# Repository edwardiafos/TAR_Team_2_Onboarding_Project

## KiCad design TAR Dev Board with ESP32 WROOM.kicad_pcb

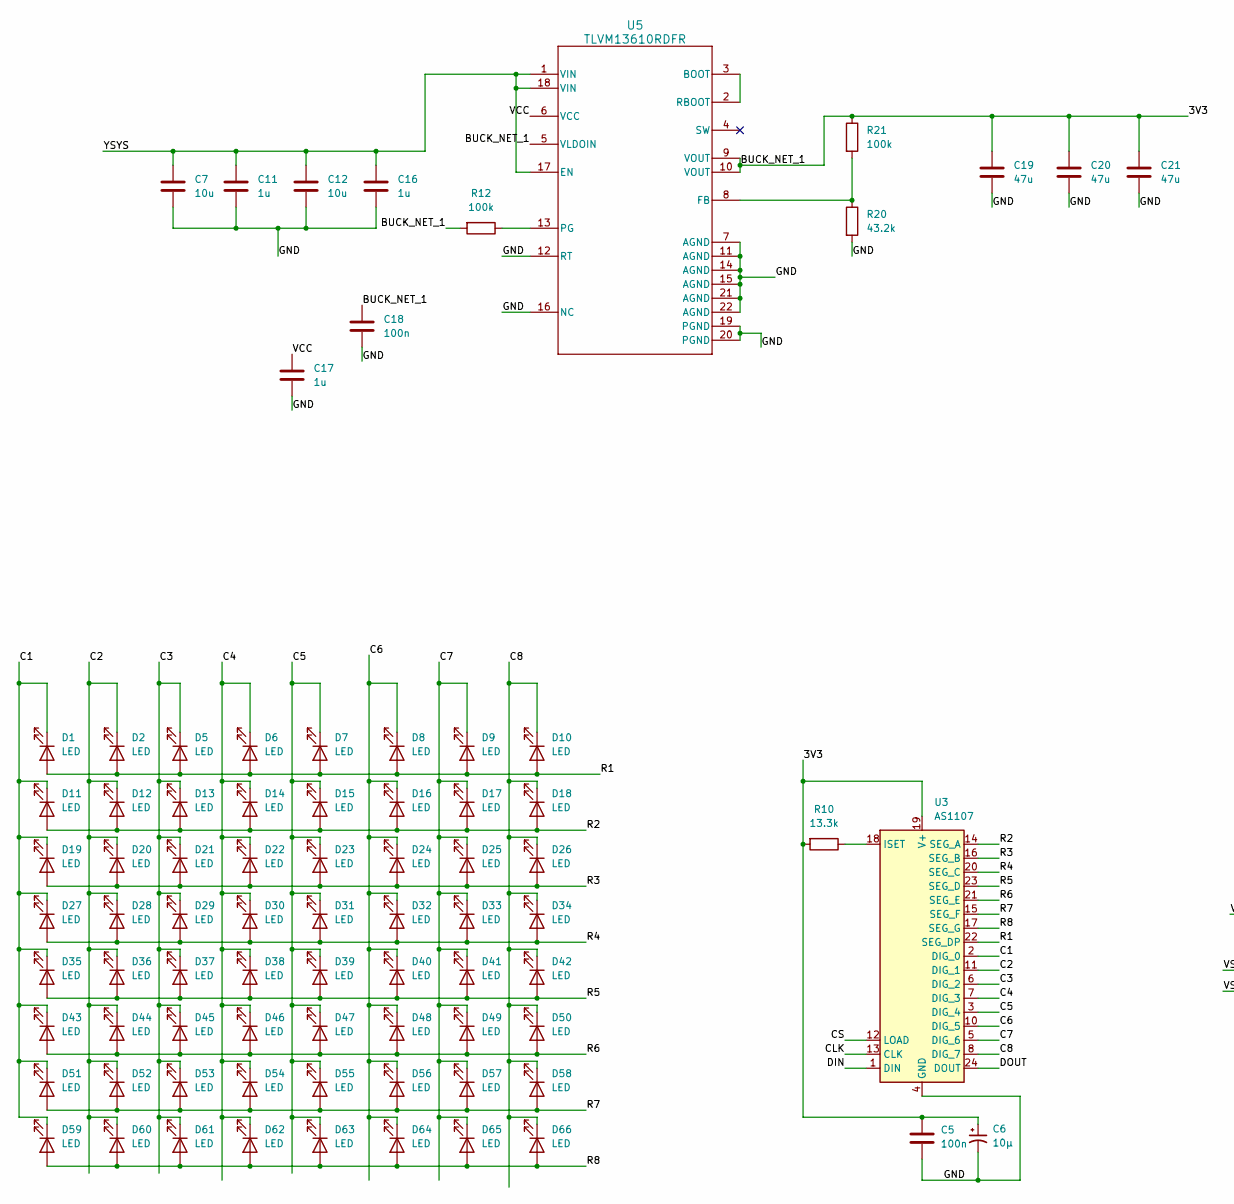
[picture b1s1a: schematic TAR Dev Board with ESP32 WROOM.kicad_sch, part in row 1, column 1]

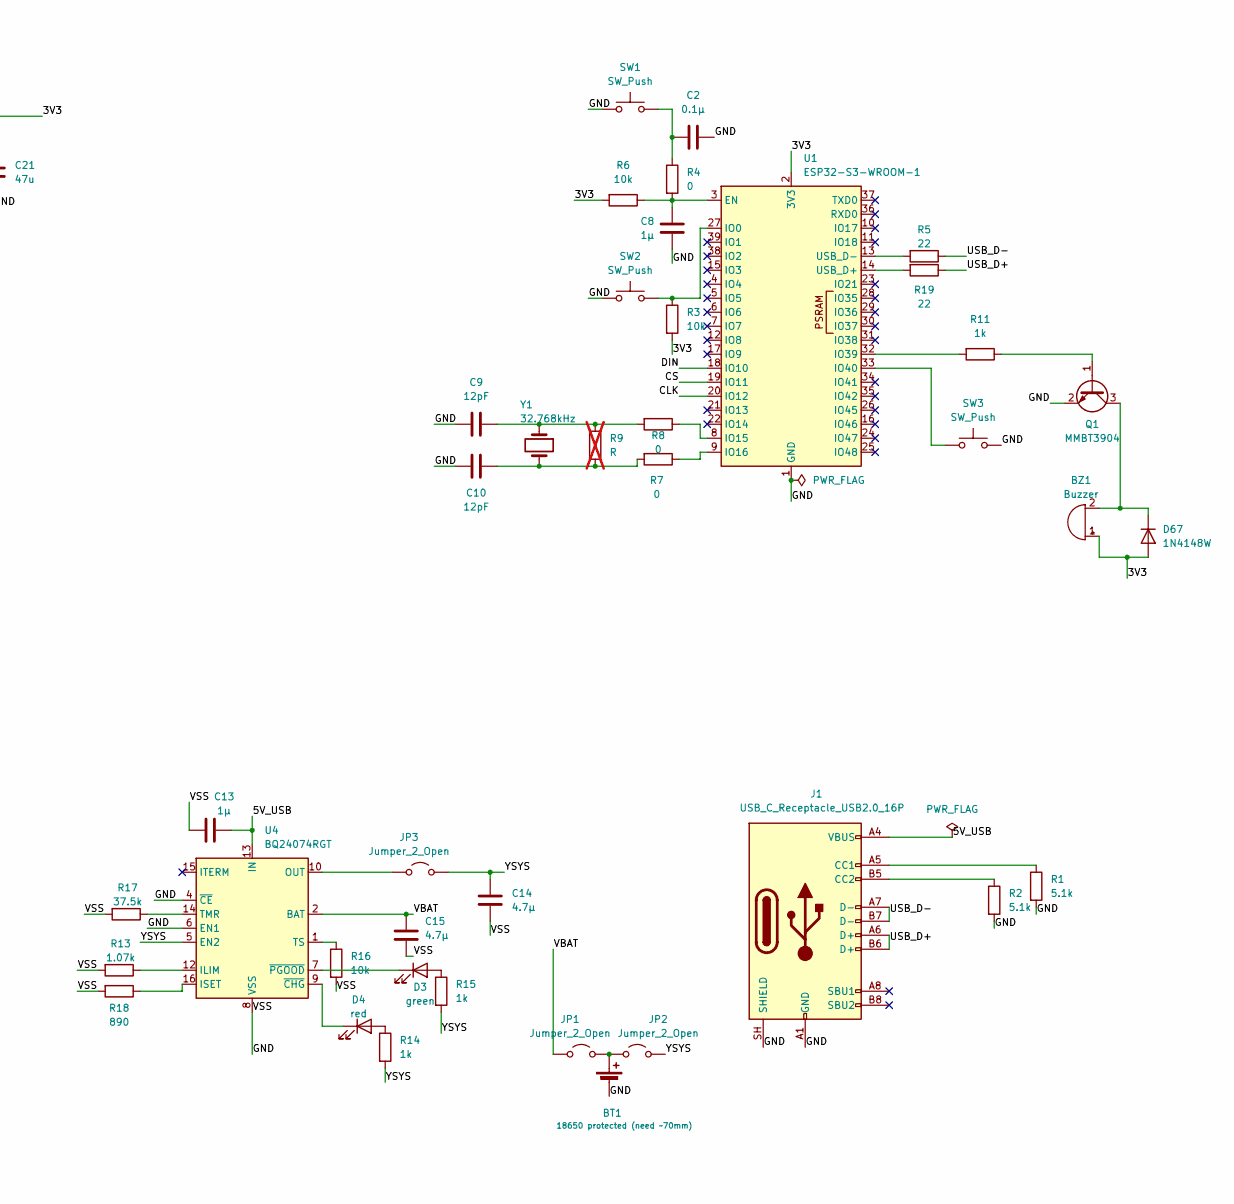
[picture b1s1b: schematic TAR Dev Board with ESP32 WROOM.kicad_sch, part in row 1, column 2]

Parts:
BT1: 18650 protected (need ~70mm); BatteryHolder_Keystone_1042_1x18650
BZ1: Buzzer; Buzzer_12x9.5RM7.6
C2: 0.1μ; C_0805_2012Metric
C5, C18: 100n; C_0805_2012Metric
C6: 10μ; CP_Elec_4x5.4
C7, C12: 10u; C_1206_3216Metric
C8: 1µ; C_0805_2012Metric
C9, C10: 12pF; C_0603_1608Metric
C11, C16, C17: 1u; C_0805_2012Metric
C13: 1μ; C_0805_2012Metric
C14, C15: 4.7μ; C_1206_3216Metric
C19, C20, C21: 47u; C_1206_3216Metric
D1, D2, D5, D6, D7, D8, D9, D10, D11, D12, D13, D14, D15, D16, D17, D18, D19, D20, D21, D22, D23, D24, D25, D26, D27, D28, D29, D30, D31, D32, D33, D34, D35, D36, D37, D38, D39, D40, D41, D42, D43, D44, D45, D46, D47, D48, D49, D50, D51, D52, D53, D54, D55, D56, D57, D58, D59, D60, D61, D62, D63, D64, D65, D66: LED; LED_0805_2012Metric
D3: green; LED_0805_2012Metric
D4: red; LED_0805_2012Metric
D67: 1N4148W; D_SOD-123
J1: USB_C_Receptacle_USB2.0_16P; USB_C_Receptacle_HRO_TYPE-C-31-M-12
JP1, JP2, JP3: Jumper_2_Open; PinHeader_1x02_P2.54mm_Vertical
Q1: MMBT3904; SOT-23
R1, R2: 5.1k; R_0805_2012Metric
R3, R6, R16: 10k; R_0805_2012Metric
R4, R7, R8: 0; R_0805_2012Metric
R5, R19: 22; R_0805_2012Metric
R9: R; R_0805_2012Metric; not fitted
R10: 13.3k; R_0805_2012Metric
R11, R14, R15: 1k; R_0805_2012Metric
R12, R21: 100k; R_0805_2012Metric
R13: 1.07k; R_0805_2012Metric
R17: 37.5k; R_0805_2012Metric
R18: 890; R_0805_2012Metric
R20: 43.2k; R_0805_2012Metric
SW1, SW2, SW3: SW_Push; SW_PUSH_6mm
U1: ESP32-S3-WROOM-1
U3: AS1107; SOIC-24W_7.5x15.4mm_P1.27mm
U4: BQ24074RGT; VQFN-16-1EP_3x3mm_P0.5mm_EP1.8x1.8mm_ThermalVias
U5: TLVM13610RDFR; TLVM13610
Y1: 32.768kHz; Crystal_SMD_3215-2Pin_3.2x1.5mm

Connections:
/5V_USB: C13.1, J1.A4 (VBUS), J1.A9 (VBUS), J1.B4 (VBUS), J1.B9 (VBUS), U4.13 (IN)
/<NO NET>: BZ1.1 (+), C5.1, C6.1, C18.1, C19.1, C20.1, C21.1, D67.2 (A), R3.2, R6.2, R10.2, R12.2, R21.1, U1.2 (3V3), U3.19 (V+), U5.5 (VLDOIN), U5.9 (VOUT), U5.10 (VOUT)
/C1: D1.1 (K), D11.1 (K), D19.1 (K), D27.1 (K), D35.1 (K), D43.1 (K), D51.1 (K), D59.1 (K), U3.2 (DIG_0)
/C2: D2.1 (K), D12.1 (K), D20.1 (K), D28.1 (K), D36.1 (K), D44.1 (K), D52.1 (K), D60.1 (K), U3.11 (DIG_1)
/C3: D5.1 (K), D13.1 (K), D21.1 (K), D29.1 (K), D37.1 (K), D45.1 (K), D53.1 (K), D61.1 (K), U3.6 (DIG_2)
/C4: D6.1 (K), D14.1 (K), D22.1 (K), D30.1 (K), D38.1 (K), D46.1 (K), D54.1 (K), D62.1 (K), U3.7 (DIG_3)
/C5: D7.1 (K), D15.1 (K), D23.1 (K), D31.1 (K), D39.1 (K), D47.1 (K), D55.1 (K), D63.1 (K), U3.3 (DIG_4)
/C6: D8.1 (K), D16.1 (K), D24.1 (K), D32.1 (K), D40.1 (K), D48.1 (K), D56.1 (K), D64.1 (K), U3.10 (DIG_5)
/C7: D9.1 (K), D17.1 (K), D25.1 (K), D33.1 (K), D41.1 (K), D49.1 (K), D57.1 (K), D65.1 (K), U3.5 (DIG_6)
/C8: D10.1 (K), D18.1 (K), D26.1 (K), D34.1 (K), D42.1 (K), D50.1 (K), D58.1 (K), D66.1 (K), U3.8 (DIG_7)
/CLK: U1.20 (IO12), U3.13 (CLK)
/CS: U1.19 (IO11), U3.12 (LOAD)
/DIN: U1.18 (IO10), U3.1 (DIN)
/DOUT: U3.24 (DOUT)
/GND: BT1.2 (-), C2.1, C5.2, C6.2, C7.2, C8.2, C9.2, C10.2, C11.2, C12.2, C13.2, C14.2, C15.2, C16.2, C17.2, C18.2, C19.2, C20.2, C21.2, J1.A1 (GND), J1.A12 (GND), J1.B1 (GND), J1.B12 (GND), J1.SH (SHIELD), Q1.2 (E), R1.2, R2.2, R13.2, R16.2, R17.2, R18.2, R20.2, SW1.1, SW2.1, SW3.2, U1.1 (GND), U1.40 (GND), U1.41 (GND), U3.4 (GND), U3.9 (GND), U4.4 (~CE), U4.6 (EN1), U4.8 (VSS), U4.17 (VSS), U5.7 (AGND), U5.11 (AGND), U5.12 (RT), U5.14 (AGND), U5.15 (AGND), U5.16 (NC), U5.19 (PGND), U5.20 (PGND), U5.21 (AGND), U5.22 (AGND)
/R1: D1.2 (A), D2.2 (A), D5.2 (A), D6.2 (A), D7.2 (A), D8.2 (A), D9.2 (A), D10.2 (A), U3.22 (SEG_DP)
/R2: D11.2 (A), D12.2 (A), D13.2 (A), D14.2 (A), D15.2 (A), D16.2 (A), D17.2 (A), D18.2 (A), U3.14 (SEG_A)
/R3: D19.2 (A), D20.2 (A), D21.2 (A), D22.2 (A), D23.2 (A), D24.2 (A), D25.2 (A), D26.2 (A), U3.16 (SEG_B)
/R4: D27.2 (A), D28.2 (A), D29.2 (A), D30.2 (A), D31.2 (A), D32.2 (A), D33.2 (A), D34.2 (A), U3.20 (SEG_C)
/R5: D35.2 (A), D36.2 (A), D37.2 (A), D38.2 (A), D39.2 (A), D40.2 (A), D41.2 (A), D42.2 (A), U3.23 (SEG_D)
/R6: D43.2 (A), D44.2 (A), D45.2 (A), D46.2 (A), D47.2 (A), D48.2 (A), D49.2 (A), D50.2 (A), U3.21 (SEG_E)
/R7: D51.2 (A), D52.2 (A), D53.2 (A), D54.2 (A), D55.2 (A), D56.2 (A), D57.2 (A), D58.2 (A), U3.15 (SEG_F)
/R8: D59.2 (A), D60.2 (A), D61.2 (A), D62.2 (A), D63.2 (A), D64.2 (A), D65.2 (A), D66.2 (A), U3.17 (SEG_G)
/USB_D+: J1.A6 (D+), J1.B6 (D+), R19.1
/USB_D-: J1.A7 (D-), J1.B7 (D-), R5.1
/VBAT: C15.1, JP1.1 (A), U4.2 (BAT), U4.3 (BAT)
/VCC: C17.1, U5.6 (VCC)
/YSYS: C7.1, C11.1, C12.1, C14.1, C16.1, JP2.2 (B), JP3.2 (B), R14.2, R15.2, U4.5 (EN2), U5.1 (VIN), U5.17 (EN), U5.18 (VIN)
unnamed: BT1.1 (+), JP1.2 (B), JP2.1 (A)
unnamed: BZ1.2 (-), D67.1 (K), Q1.3 (C)
unnamed: C2.2, R4.1, SW1.2
unnamed: C9.1, R8.2, R9.1, Y1.1
unnamed: C10.1, R7.2, R9.2, Y1.2
unnamed: D3.2 (A), R15.1
unnamed: D3.1 (K), U4.7 (~PGOOD)
unnamed: D4.2 (A), R14.1
unnamed: D4.1 (K), U4.9 (~CHG)
unnamed: J1.A5 (CC1), R1.1
unnamed: J1.B5 (CC2), R2.1
unnamed: JP3.1 (A), U4.10 (OUT), U4.11 (OUT)
unnamed: Q1.1 (B), R11.1
unnamed: C8.1, R4.2, R6.1, U1.3 (EN)
unnamed: R3.1, SW2.2, U1.27 (IO0)
unnamed: R8.1, U1.8 (IO15)
unnamed: R7.1, U1.9 (IO16)
unnamed: R11.2, U1.32 (IO39)
unnamed: SW3.1, U1.33 (IO40)
unnamed: R19.2, U1.14 (USB_D+)
unnamed: R5.2, U1.13 (USB_D-)
unnamed: R10.1, U3.18 (ISET)
unnamed: R13.1, U4.12 (ILIM)
unnamed: R18.1, U4.16 (ISET)
unnamed: R17.1, U4.14 (TMR)
unnamed: R16.1, U4.1 (TS)
unnamed: U5.2 (RBOOT), U5.3 (BOOT)
unnamed: R20.1, R21.2, U5.8 (FB)
unnamed: R12.1, U5.13 (PG)

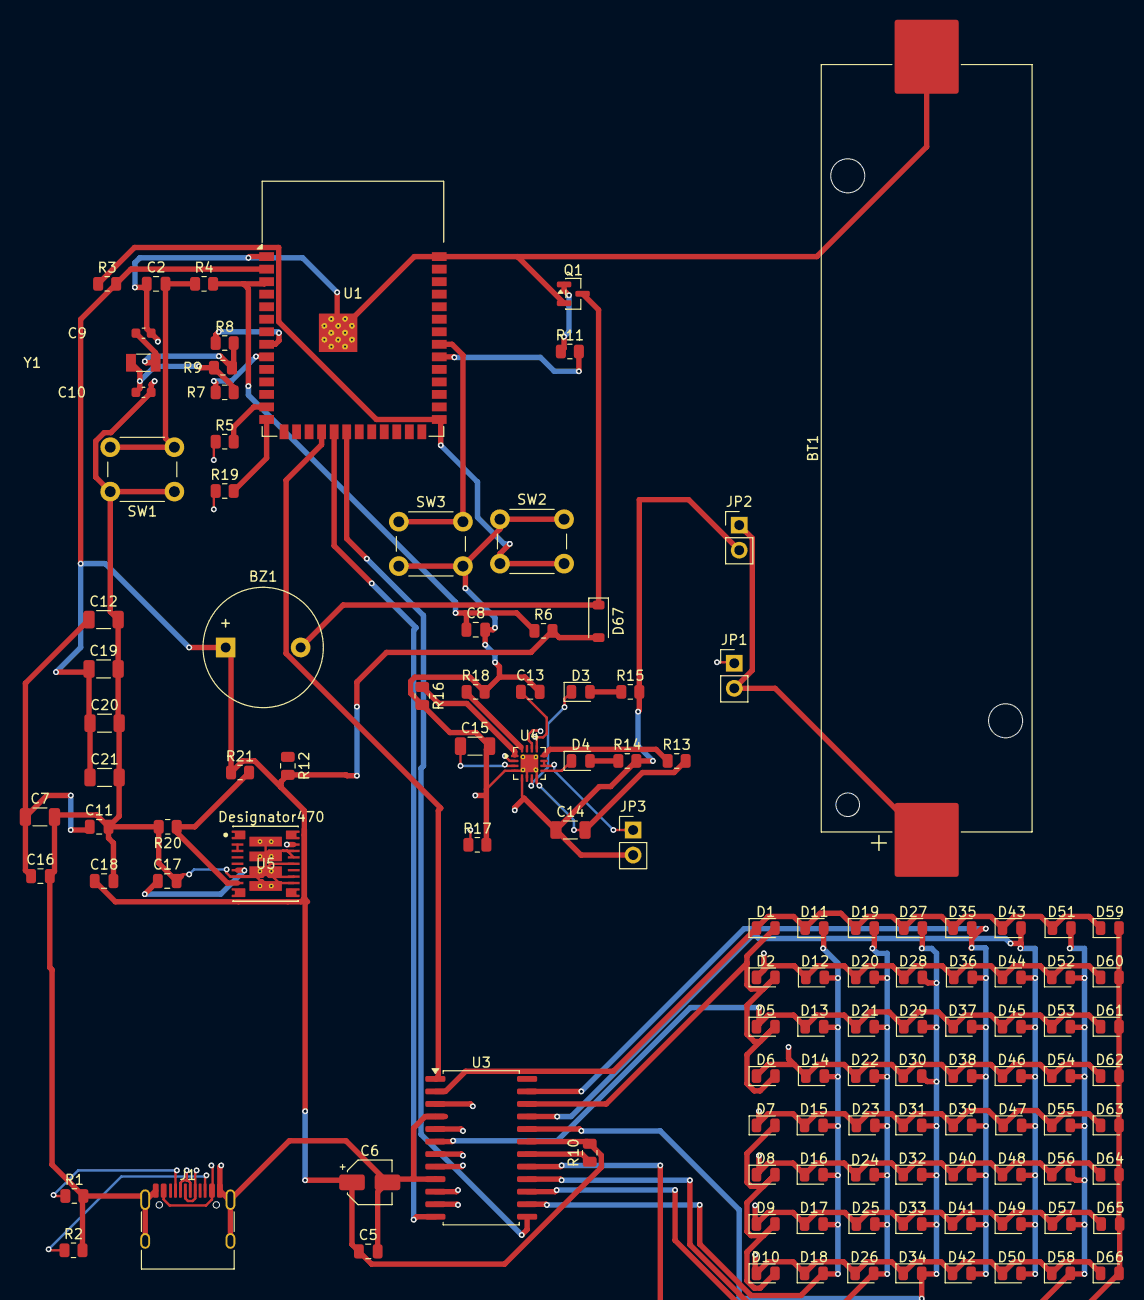
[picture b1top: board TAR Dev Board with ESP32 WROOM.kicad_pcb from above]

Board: 4 copper layers, 121 parts (0 on the bottom side), 56 nets.
